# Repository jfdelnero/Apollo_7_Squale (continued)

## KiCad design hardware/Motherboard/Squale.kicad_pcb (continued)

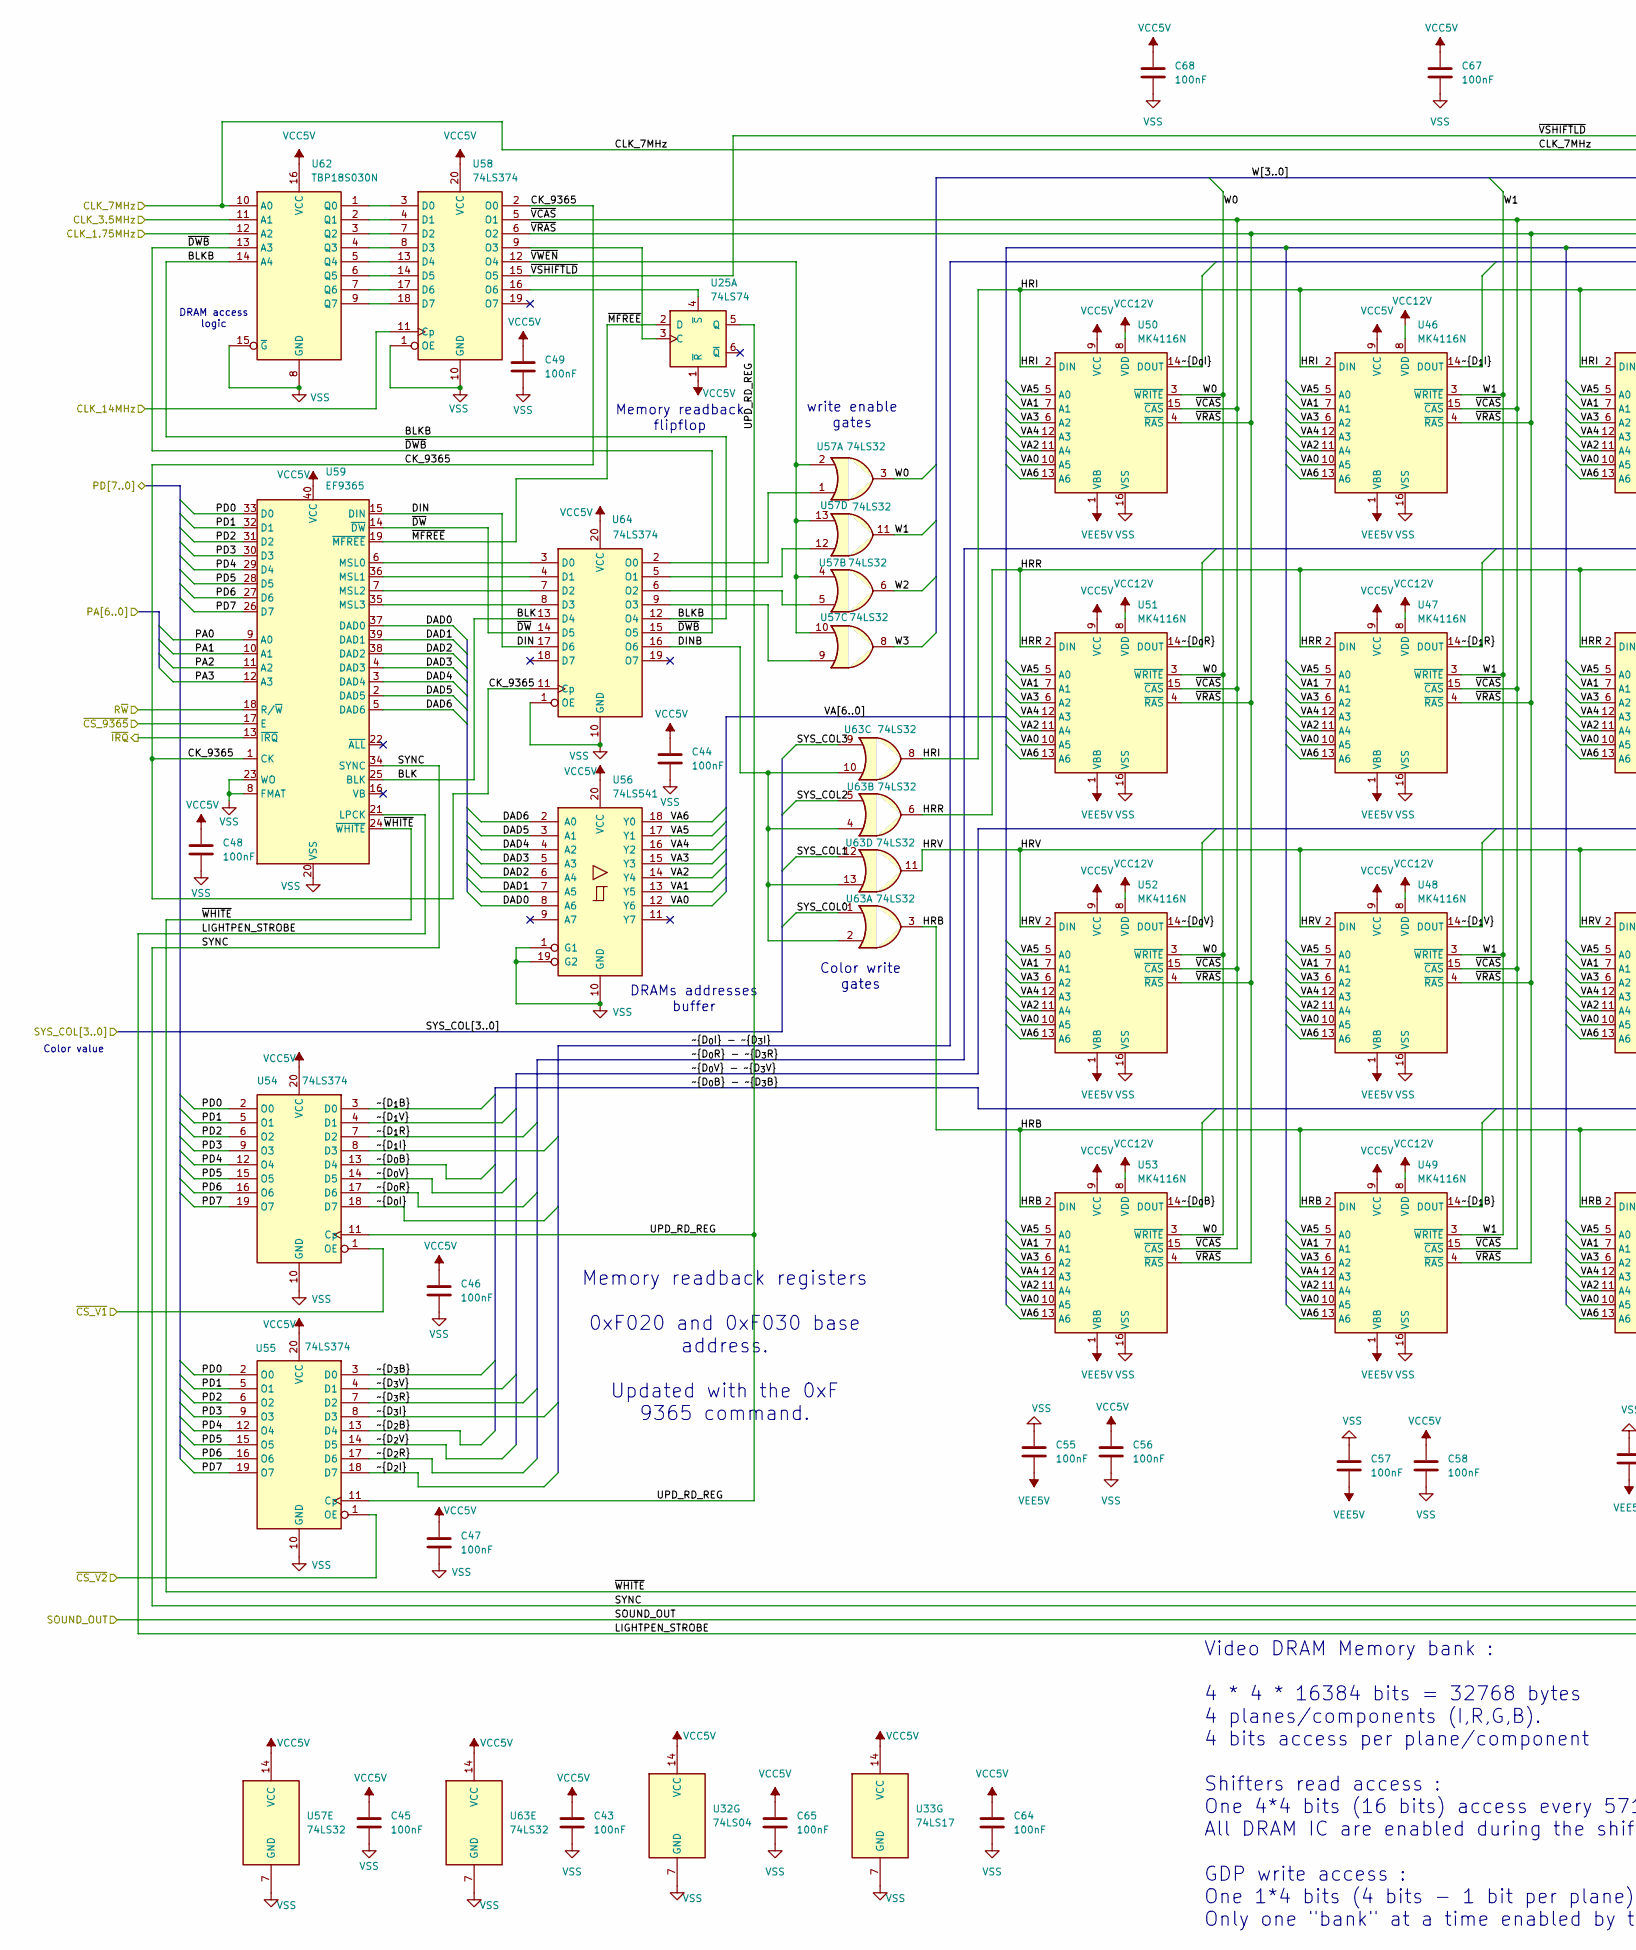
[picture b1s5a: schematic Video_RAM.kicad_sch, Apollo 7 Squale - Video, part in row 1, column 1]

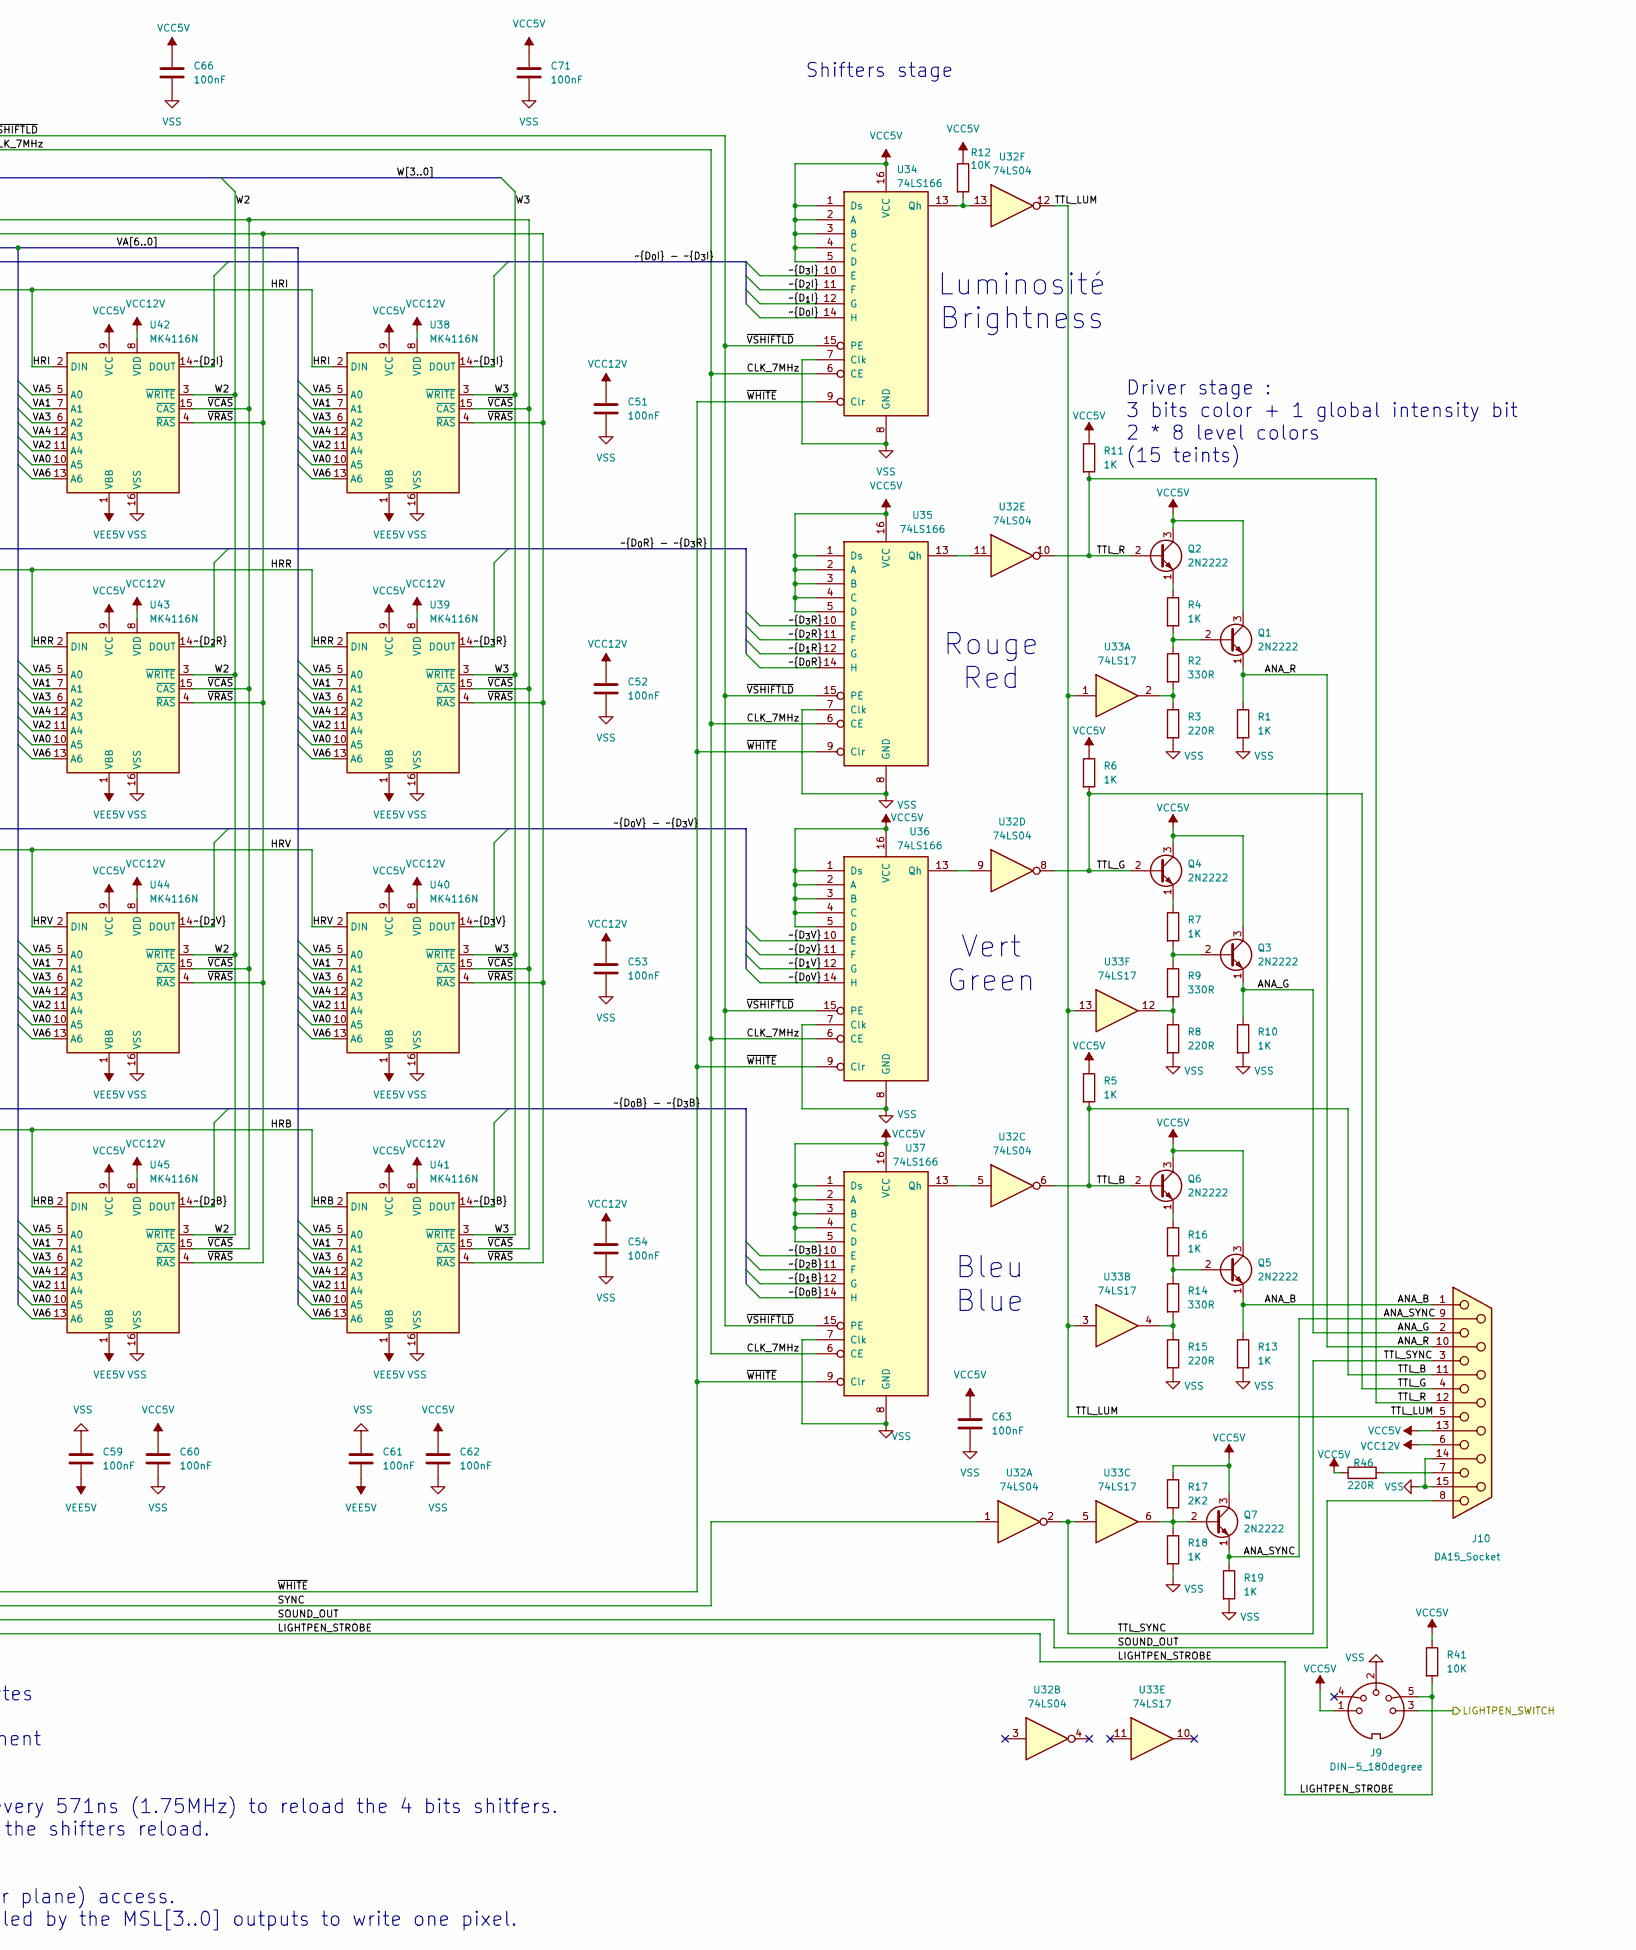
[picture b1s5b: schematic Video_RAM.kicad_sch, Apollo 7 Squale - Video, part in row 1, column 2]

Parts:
C43, C44, C45, C46, C47, C48, C49, C51, C52, C53, C54, C55, C56, C57, C58, C59, C60, C61, C62, C63, C64, C65, C66, C67, C68, C71: 100nF; C_Disc_D9.0mm_W2.5mm_P5.00mm
J9: DIN-5_180degree; DIN5-RA-PTH
J10: DA15_Socket; DSUB-15_Socket_Horizontal_P2.77x2.84mm_EdgePinOffset9.40mm
Q1, Q2, Q3, Q4, Q5, Q6, Q7: 2N2222; TO-18-3
R1, R4, R5, R6, R7, R10, R11, R13, R16, R18, R19: 1K; R_Axial_DIN0309_L9.0mm_D3.2mm_P12.70mm_Horizontal
R2, R9, R14: 330R; R_Axial_DIN0309_L9.0mm_D3.2mm_P12.70mm_Horizontal
R3, R8, R15, R46: 220R; R_Axial_DIN0309_L9.0mm_D3.2mm_P12.70mm_Horizontal
R12, R41: 10K; R_Axial_DIN0309_L9.0mm_D3.2mm_P12.70mm_Horizontal
R17: 2K2; R_Axial_DIN0309_L9.0mm_D3.2mm_P12.70mm_Horizontal
U25: 74LS74; DIP-14_W7.62mm_Socket
U32: 74LS04; DIP-14_W7.62mm_Socket
U33: 74LS17; DIP-14_W7.62mm_Socket
U34, U35, U36, U37: 74LS166; DIP-16_W7.62mm_Socket
U38, U39, U40, U41, U42, U43, U44, U45, U46, U47, U48, U49, U50, U51, U52, U53: MK4116N; DIP-16_W7.62mm_Socket
U54, U55, U58, U64: 74LS374; DIP-20_W7.62mm_Socket
U56: 74LS541; DIP-20_W7.62mm_Socket
U57, U63: 74LS32; DIP-14_W7.62mm_Socket
U59: EF9365; DIP-40_W15.24mm_Socket
U62: TBP18S030N; DIP-16_W7.62mm_Socket

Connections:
/CPU/CLK_3.5MHz: U62.11 (A1); also elsewhere on the board
/CPU/R~W: U59.18 (R/~W); also elsewhere on the board
/CPU/~CS_9365: U59.17 (E); also elsewhere on the board
/CPU/~CS_V1: U54.1 (OE); also elsewhere on the board
/CPU/~CS_V2: U55.1 (OE); also elsewhere on the board
/CPU/~IRQ: U59.13 (~IRQ); also elsewhere on the board
/Clocks/CLK_1.75MHz: U62.12 (A2); also elsewhere on the board
/Clocks/CLK_7MHz: U34.6 (CE), U35.6 (CE), U36.6 (CE), U37.6 (CE), U62.10 (A0); also elsewhere on the board
/Clocks/CLK_14MHz: U58.11 (Cp); also elsewhere on the board
/PA0: U59.9 (A0); also elsewhere on the board
/PA1: U59.10 (A1); also elsewhere on the board
/PA2: U59.11 (A2); also elsewhere on the board
/PA3: U59.12 (A3); also elsewhere on the board
/PD0: U54.2 (O0), U55.2 (O0), U59.33 (D0); also elsewhere on the board
/PD1: U54.5 (O1), U55.5 (O1), U59.32 (D1); also elsewhere on the board
/PD2: U54.6 (O2), U55.6 (O2), U59.31 (D2); also elsewhere on the board
/PD3: U54.9 (O3), U55.9 (O3), U59.30 (D3); also elsewhere on the board
/PD4: U54.12 (O4), U55.12 (O4), U59.29 (D4); also elsewhere on the board
/PD5: U54.15 (O5), U55.15 (O5), U59.28 (D5); also elsewhere on the board
/PD6: U54.16 (O6), U55.16 (O6), U59.27 (D6); also elsewhere on the board
/PD7: U54.19 (O7), U55.19 (O7), U59.26 (D7); also elsewhere on the board
/Sound/LIGHTPEN_SWITCH: J9.3; also elsewhere on the board
/Sound/SOUND_OUT: J10.8; also elsewhere on the board
/Video Controller/<NO NET>: U57.9, U64.9 (O3)
/Video Controller/ANA_B: J10.1, Q5.1 (E), R13.1
/Video Controller/ANA_G: J10.2, Q3.1 (E), R10.1
/Video Controller/ANA_R: J10.10, Q1.1 (E), R1.1
/Video Controller/ANA_SYNC: J10.9, Q7.1 (E), R19.1
/Video Controller/BLK: U59.25 (BLK), U64.13 (D4)
/Video Controller/BLKB: U62.14 (A4), U64.12 (O4)
/Video Controller/CK_9365: U58.2 (O0), U59.1 (CK), U64.11 (Cp)
/Video Controller/DAD0: U56.8 (A6), U59.37 (DAD0)
/Video Controller/DAD1: U56.7 (A5), U59.39 (DAD1)
/Video Controller/DAD2: U56.6 (A4), U59.38 (DAD2)
/Video Controller/DAD3: U56.5 (A3), U59.4 (DAD3)
/Video Controller/DAD4: U56.4 (A2), U59.3 (DAD4)
/Video Controller/DAD5: U56.3 (A1), U59.2 (DAD5)
/Video Controller/DAD6: U56.2 (A0), U59.5 (DAD6)
/Video Controller/DIN: U59.15 (DIN), U64.17 (D6)
/Video Controller/DINB: U63.2, U63.4, U63.10, U63.13, U64.16 (O6)
/Video Controller/HRB: U41.2 (DIN), U45.2 (DIN), U49.2 (DIN), U53.2 (DIN), U63.3
/Video Controller/HRI: U38.2 (DIN), U42.2 (DIN), U46.2 (DIN), U50.2 (DIN), U63.8
/Video Controller/HRR: U39.2 (DIN), U43.2 (DIN), U47.2 (DIN), U51.2 (DIN), U63.6
/Video Controller/HRV: U40.2 (DIN), U44.2 (DIN), U48.2 (DIN), U52.2 (DIN), U63.11
/Video Controller/LIGHTPEN_STROBE: J9.5, R41.2, U59.21 (LPCK)
/Video Controller/SYNC: U32.1, U59.34 (SYNC)
/Video Controller/SYS_COL0: U63.1; also elsewhere on the board
/Video Controller/SYS_COL1: U63.12; also elsewhere on the board
/Video Controller/SYS_COL2: U63.5; also elsewhere on the board
/Video Controller/SYS_COL3: U63.9; also elsewhere on the board
/Video Controller/TTL_B: J10.11 (P111), Q6.2 (B), R5.2, U32.6
/Video Controller/TTL_G: J10.4, Q4.2 (B), R6.2, U32.8
/Video Controller/TTL_LUM: J10.5, U32.12, U33.1, U33.3, U33.13
/Video Controller/TTL_R: J10.12, Q2.2 (B), R11.2, U32.10
/Video Controller/TTL_SYNC: J10.3, U32.2, U33.5
/Video Controller/UPD_RD_REG: U25.5 (Q), U54.11 (Cp), U55.11 (Cp)
/Video Controller/VA0: U38.10 (A5), U39.10 (A5), U40.10 (A5), U41.10 (A5), U42.10 (A5), U43.10 (A5), U44.10 (A5), U45.10 (A5), U46.10 (A5), U47.10 (A5), U48.10 (A5), U49.10 (A5), U50.10 (A5), U51.10 (A5), U52.10 (A5), U53.10 (A5), U56.12 (Y6)
/Video Controller/VA1: U38.7 (A1), U39.7 (A1), U40.7 (A1), U41.7 (A1), U42.7 (A1), U43.7 (A1), U44.7 (A1), U45.7 (A1), U46.7 (A1), U47.7 (A1), U48.7 (A1), U49.7 (A1), U50.7 (A1), U51.7 (A1), U52.7 (A1), U53.7 (A1), U56.13 (Y5)
/Video Controller/VA2: U38.11 (A4), U39.11 (A4), U40.11 (A4), U41.11 (A4), U42.11 (A4), U43.11 (A4), U44.11 (A4), U45.11 (A4), U46.11 (A4), U47.11 (A4), U48.11 (A4), U49.11 (A4), U50.11 (A4), U51.11 (A4), U52.11 (A4), U53.11 (A4), U56.14 (Y4)
/Video Controller/VA3: U38.6 (A2), U39.6 (A2), U40.6 (A2), U41.6 (A2), U42.6 (A2), U43.6 (A2), U44.6 (A2), U45.6 (A2), U46.6 (A2), U47.6 (A2), U48.6 (A2), U49.6 (A2), U50.6 (A2), U51.6 (A2), U52.6 (A2), U53.6 (A2), U56.15 (Y3)
/Video Controller/VA4: U38.12 (A3), U39.12 (A3), U40.12 (A3), U41.12 (A3), U42.12 (A3), U43.12 (A3), U44.12 (A3), U45.12 (A3), U46.12 (A3), U47.12 (A3), U48.12 (A3), U49.12 (A3), U50.12 (A3), U51.12 (A3), U52.12 (A3), U53.12 (A3), U56.16 (Y2)
/Video Controller/VA5: U38.5 (A0), U39.5 (A0), U40.5 (A0), U41.5 (A0), U42.5 (A0), U43.5 (A0), U44.5 (A0), U45.5 (A0), U46.5 (A0), U47.5 (A0), U48.5 (A0), U49.5 (A0), U50.5 (A0), U51.5 (A0), U52.5 (A0), U53.5 (A0), U56.17 (Y1)
/Video Controller/VA6: U38.13 (A6), U39.13 (A6), U40.13 (A6), U41.13 (A6), U42.13 (A6), U43.13 (A6), U44.13 (A6), U45.13 (A6), U46.13 (A6), U47.13 (A6), U48.13 (A6), U49.13 (A6), U50.13 (A6), U51.13 (A6), U52.13 (A6), U53.13 (A6), U56.18 (Y0)
/Video Controller/W0: U50.3 (~WRITE), U51.3 (~WRITE), U52.3 (~WRITE), U53.3 (~WRITE), U57.3
/Video Controller/W1: U46.3 (~WRITE), U47.3 (~WRITE), U48.3 (~WRITE), U49.3 (~WRITE), U57.11
/Video Controller/W2: U42.3 (~WRITE), U43.3 (~WRITE), U44.3 (~WRITE), U45.3 (~WRITE), U57.6
/Video Controller/W3: U38.3 (~WRITE), U39.3 (~WRITE), U40.3 (~WRITE), U41.3 (~WRITE), U57.8
/Video Controller/~DWB: U62.13 (A3), U64.15 (O5)
/Video Controller/~DW: U59.14 (~DW), U64.14 (D5)
/Video Controller/~D_{0B}: U37.14 (H), U53.14 (DOUT), U54.13 (D4)
/Video Controller/~D_{0I}: U34.14 (H), U50.14 (DOUT), U54.18 (D7)
/Video Controller/~D_{0R}: U35.14 (H), U51.14 (DOUT), U54.17 (D6)
/Video Controller/~D_{0V}: U36.14 (H), U52.14 (DOUT), U54.14 (D5)
/Video Controller/~D_{1B}: U37.12 (G), U49.14 (DOUT), U54.3 (D0)
/Video Controller/~D_{1I}: U34.12 (G), U46.14 (DOUT), U54.8 (D3)
/Video Controller/~D_{1R}: U35.12 (G), U47.14 (DOUT), U54.7 (D2)
/Video Controller/~D_{1V}: U36.12 (G), U48.14 (DOUT), U54.4 (D1)
/Video Controller/~D_{2B}: U37.11 (F), U45.14 (DOUT), U55.13 (D4)
/Video Controller/~D_{2I}: U34.11 (F), U42.14 (DOUT), U55.18 (D7)
/Video Controller/~D_{2R}: U35.11 (F), U43.14 (DOUT), U55.17 (D6)
/Video Controller/~D_{2V}: U36.11 (F), U44.14 (DOUT), U55.14 (D5)
/Video Controller/~D_{3B}: U37.10 (E), U41.14 (DOUT), U55.3 (D0)
/Video Controller/~D_{3I}: U34.10 (E), U38.14 (DOUT), U55.8 (D3)
/Video Controller/~D_{3R}: U35.10 (E), U39.14 (DOUT), U55.7 (D2)
/Video Controller/~D_{3V}: U36.10 (E), U40.14 (DOUT), U55.4 (D1)
/Video Controller/~MFREE: U25.2 (D), U59.19 (~MFREE)
/Video Controller/~VCAS: U38.15 (~CAS), U39.15 (~CAS), U40.15 (~CAS), U41.15 (~CAS), U42.15 (~CAS), U43.15 (~CAS), U44.15 (~CAS), U45.15 (~CAS), U46.15 (~CAS), U47.15 (~CAS), U48.15 (~CAS), U49.15 (~CAS), U50.15 (~CAS), U51.15 (~CAS), U52.15 (~CAS), U53.15 (~CAS), U58.5 (O1)
/Video Controller/~VRAS: U38.4 (~RAS), U39.4 (~RAS), U40.4 (~RAS), U41.4 (~RAS), U42.4 (~RAS), U43.4 (~RAS), U44.4 (~RAS), U45.4 (~RAS), U46.4 (~RAS), U47.4 (~RAS), U48.4 (~RAS), U49.4 (~RAS), U50.4 (~RAS), U51.4 (~RAS), U52.4 (~RAS), U53.4 (~RAS), U58.6 (O2)
/Video Controller/~VSHIFTLD: U34.15 (PE), U35.15 (PE), U36.15 (PE), U37.15 (PE), U58.15 (O5)
/Video Controller/~VWEN: U57.2, U57.4, U57.10, U57.13, U58.12 (O4)
/Video Controller/~WHITE: U34.9 (Clr), U35.9 (Clr), U36.9 (Clr), U37.9 (Clr), U59.24 (~WHITE)
unnamed: J10.7, R46.2
unnamed: Q1.2 (B), R2.1, R4.2
unnamed: Q2.1 (E), R4.1
unnamed: Q3.2 (B), R7.2, R9.1
unnamed: Q4.1 (E), R7.1
unnamed: Q5.2 (B), R14.1, R16.2
unnamed: Q6.1 (E), R16.1
unnamed: Q7.2 (B), R17.2, R18.1, U33.6
unnamed: R2.2, R3.1, U33.2
unnamed: R8.1, R9.2, U33.12
unnamed: R14.2, R15.1, U33.4
unnamed: U25.3 (C), U58.9 (O3)
unnamed: U25.4 (~S), U58.16 (O6)
unnamed: R12.2, U32.13, U34.13 (Qh)
unnamed: U32.11, U35.13 (Qh)
unnamed: U32.9, U36.13 (Qh)
unnamed: U32.5, U37.13 (Qh)
unnamed: U58.3 (D0), U62.1 (Q0)
unnamed: U58.4 (D1), U62.2 (Q1)
unnamed: U58.7 (D2), U62.3 (Q2)
unnamed: U58.8 (D3), U62.4 (Q3)
unnamed: U58.13 (D4), U62.5 (Q4)
unnamed: U58.14 (D5), U62.6 (Q5)
unnamed: U58.17 (D6), U62.7 (Q6)
unnamed: U58.18 (D7), U62.9 (Q7)
unnamed: U59.6 (MSL0), U64.3 (D0)
unnamed: U59.36 (MSL1), U64.4 (D1)
unnamed: U59.7 (MSL2), U64.7 (D2)
unnamed: U59.35 (MSL3), U64.8 (D3)
unnamed: U57.1, U64.2 (O0)
unnamed: U57.12, U64.5 (O1)
unnamed: U57.5, U64.6 (O2)
VCC5V: C43.1, C44.1, C45.1, C46.1, C47.1, C48.1, C49.1, C56.1, C58.1, C60.1, C62.1, C63.1, C64.1, C65.1, C66.1, C67.1, C68.1, C71.1, J9.1, J10.13, Q1.3 (C), Q2.3 (C), Q3.3 (C), Q4.3 (C), Q5.3 (C), Q6.3 (C), Q7.3 (C), R5.1, R6.1, R11.1, R12.1, R17.1, R41.1, R46.1, U25.1 (~R), U32.14 (VCC), U33.14 (VCC), U34.1 (Ds), U34.2 (A), U34.3 (B), U34.4 (C), U34.5 (D), U34.16 (VCC), U35.1 (Ds), U35.2 (A), U35.3 (B), U35.4 (C), U35.5 (D), U35.16 (VCC), U36.1 (Ds), U36.2 (A), U36.3 (B), U36.4 (C), U36.5 (D), U36.16 (VCC), U37.1 (Ds), U37.2 (A), U37.3 (B), U37.4 (C), U37.5 (D), U37.16 (VCC), U38.9 (VCC), U39.9 (VCC), U40.9 (VCC), U41.9 (VCC), U42.9 (VCC), U43.9 (VCC), U44.9 (VCC), U45.9 (VCC), U46.9 (VCC), U47.9 (VCC), U48.9 (VCC), U49.9 (VCC), U50.9 (VCC), U51.9 (VCC), U52.9 (VCC), U53.9 (VCC), U54.20 (VCC), U55.20 (VCC), U56.20 (VCC), U57.14 (VCC), U58.20 (VCC), U59.40 (VCC), U62.16 (VCC), U63.14 (VCC), U64.20 (VCC); also elsewhere on the board
VCC12V: C51.1, C52.1, C53.1, C54.1, J10.6, U38.8 (VDD), U39.8 (VDD), U40.8 (VDD), U41.8 (VDD), U42.8 (VDD), U43.8 (VDD), U44.8 (VDD), U45.8 (VDD), U46.8 (VDD), U47.8 (VDD), U48.8 (VDD), U49.8 (VDD), U50.8 (VDD), U51.8 (VDD), U52.8 (VDD), U53.8 (VDD); also elsewhere on the board
VEE5V: C55.2, C57.2, C59.2, C61.2, U38.1 (VBB), U39.1 (VBB), U40.1 (VBB), U41.1 (VBB), U42.1 (VBB), U43.1 (VBB), U44.1 (VBB), U45.1 (VBB), U46.1 (VBB), U47.1 (VBB), U48.1 (VBB), U49.1 (VBB), U50.1 (VBB), U51.1 (VBB), U52.1 (VBB), U53.1 (VBB); also elsewhere on the board
VSS: C43.2, C44.2, C45.2, C46.2, C47.2, C48.2, C49.2, C51.2, C52.2, C53.2, C54.2, C55.1, C56.2, C57.1, C58.2, C59.1, C60.2, C61.1, C62.2, C63.2, C64.2, C65.2, C66.2, C67.2, C68.2, C71.2, J9.2, J10.14, J10.15, R1.2, R3.2, R8.2, R10.2, R13.2, R15.2, R18.2, R19.2, U32.7 (GND), U33.7 (GND), U34.7 (Clk), U34.8 (GND), U35.7 (Clk), U35.8 (GND), U36.7 (Clk), U36.8 (GND), U37.7 (Clk), U37.8 (GND), U38.16 (VSS), U39.16 (VSS), U40.16 (VSS), U41.16 (VSS), U42.16 (VSS), U43.16 (VSS), U44.16 (VSS), U45.16 (VSS), U46.16 (VSS), U47.16 (VSS), U48.16 (VSS), U49.16 (VSS), U50.16 (VSS), U51.16 (VSS), U52.16 (VSS), U53.16 (VSS), U54.10 (GND), U55.10 (GND), U56.1 (G1), U56.10 (GND), U56.19 (G2), U57.7 (GND), U58.1 (OE), U58.10 (GND), U59.8 (FMAT), U59.20 (VSS), U59.23 (WO), U62.8 (GND), U62.15 (~G), U63.7 (GND), U64.1 (OE), U64.10 (GND); also elsewhere on the board

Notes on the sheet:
DRAMs addresses buffer
Luminosité Brightness
Memory readback registers 0xF020 and 0xF030 base address. Updated with the 0xF 9365 command.
Shifters stage
write enable gates
DRAM access logic
Rouge Red
Bleu Blue
Color write gates
Color value
Driver stage : 3 bits color + 1 global intensity bit 2 * 8 level colors (15 teints)
Memory readback flipflop
Vert Green
Video DRAM Memory bank : 4 * 4 * 16384 bits = 32768 bytes 4 planes/components (I,R,G,B). 4 bits access per plane/component Shifters read access : One 4*4 bits (16 bits) access every 571ns (1.75MHz) to reload the 4 bits shitfers. All DRAM IC are enabled during the shifters reload. GDP write access :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

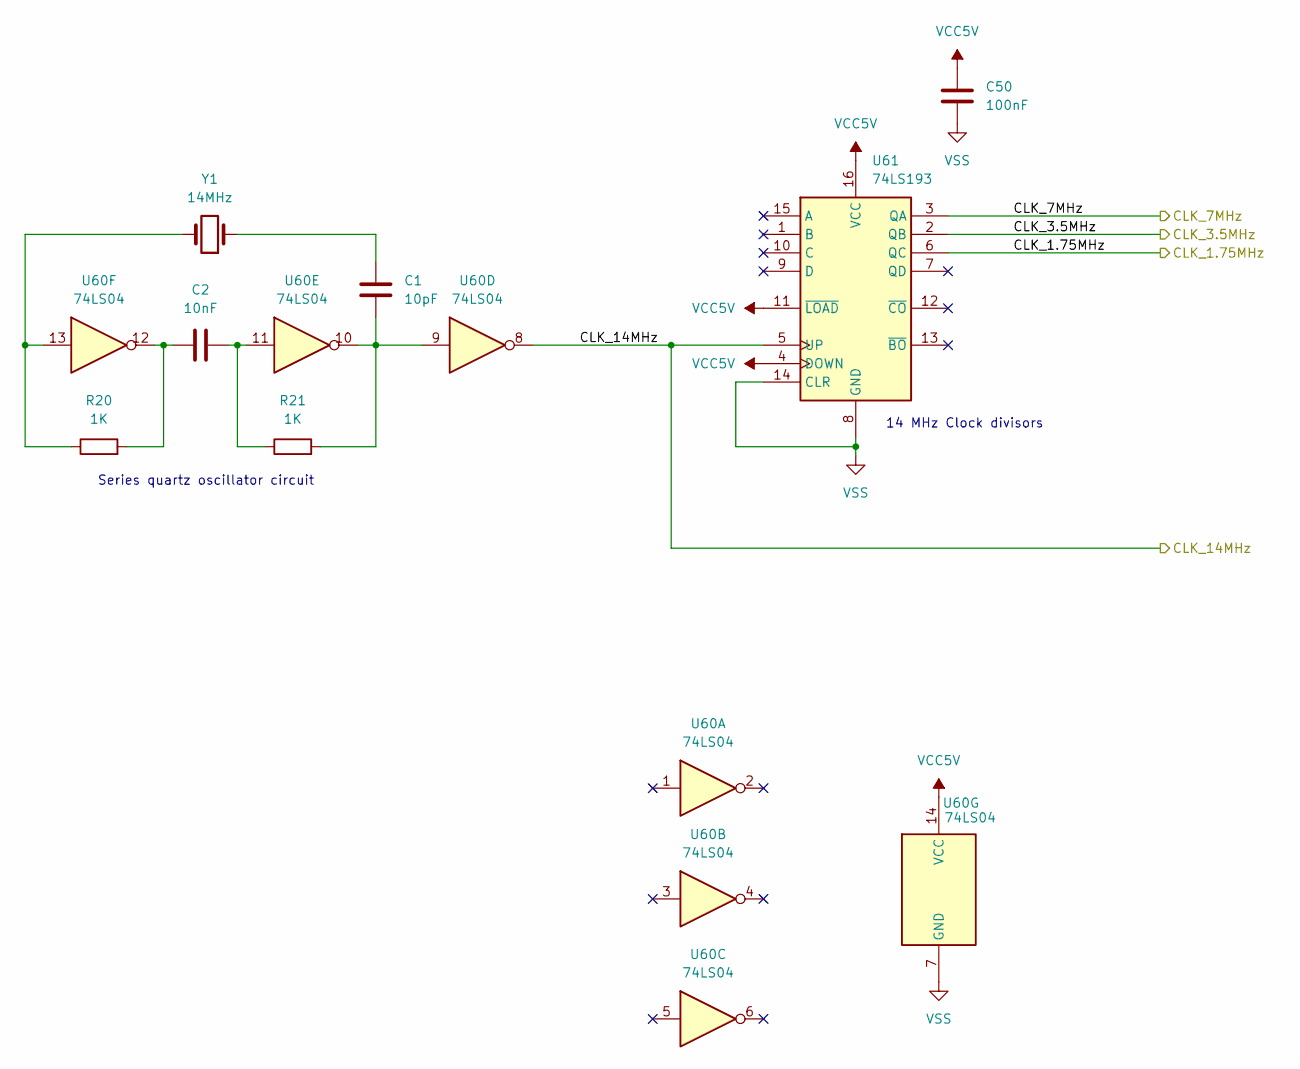
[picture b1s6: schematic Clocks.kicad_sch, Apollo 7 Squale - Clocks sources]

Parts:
C1: 10pF; C_Disc_D3.0mm_W1.6mm_P2.50mm
C2: 10nF; C_Disc_D9.0mm_W2.5mm_P5.00mm
C50: 100nF; C_Disc_D9.0mm_W2.5mm_P5.00mm
R20, R21: 1K; R_Axial_DIN0309_L9.0mm_D3.2mm_P12.70mm_Horizontal
U60: 74LS04; DIP-14_W7.62mm_Socket
U61: 74LS193; DIP-16_W7.62mm_Socket
Y1: 14MHz; Crystal_HC18-U_Vertical

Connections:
/CPU/CLK_3.5MHz: U61.2 (QB); also elsewhere on the board
/Clocks/CLK_1.75MHz: U61.6 (QC); also elsewhere on the board
/Clocks/CLK_7MHz: U61.3 (QA); also elsewhere on the board
/Clocks/CLK_14MHz: U60.8, U61.5 (UP); also elsewhere on the board
unnamed: C1.1, Y1.1
unnamed: C1.2, R21.2, U60.9, U60.10
unnamed: C2.1, R20.2, U60.12
unnamed: C2.2, R21.1, U60.11
unnamed: R20.1, U60.13, Y1.2
VCC5V: C50.1, U60.14 (VCC), U61.4 (DOWN), U61.11 (~LOAD), U61.16 (VCC); also elsewhere on the board
VSS: C50.2, U60.7 (GND), U61.8 (GND), U61.14 (CLR); also elsewhere on the board

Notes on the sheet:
Series quartz oscillator circuit
14 MHz Clock divisors
